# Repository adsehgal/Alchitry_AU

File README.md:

# Alchitry AU Shields
### Aditya Sehgal

</p>This repo is a compilation of custom shields I have designed for the Alchitry AU FPGA.</br>
The following is a list of shields I have designed:</p>
  <il>
   
 - [Alchitry PCB Template : ](https://github.com/adsehgal/Alchitry_AU/tree/master/KiCad_Template_Alchitry_Base_Top_Bot) KiCad template for the FPGA board, provided by Alchitry

 - [I/O Shield with HDMI : ](https://github.com/adsehgal/Alchitry_AU/tree/master/IO_Shield_W_HDMI) I/O shield with a variety of peripherals including an LED matrix and HDMI. Uses original Alchitry connectors
 - [Play Shield : ](https://github.com/adsehgal/Alchitry_AU/tree/master/Alchitry_Play_Shield) Shield designed to work like a controller with two sets of directional arrow keys, 7-segment displays, LED array and HDMI.

 The following is a list of boards I designed with a 1mm pitch connector instead of the original connectors that Alchitry uses:
  - [Connector Adaptor :](https://github.com/adsehgal/Alchitry_AU/tree/master/Alchitry_AU_Connector_Adaptor) Adaptor board to convert the 0.5mm standard mezzanine connectors to 1mm pitch connectors
 - [I/O Shield with 1mm connectors :](https://github.com/adsehgal/Alchitry_AU/tree/master/Alchitry_AU_NonStandard_IO) I/O shield with a variety of peripherals, used in conjunction with ["Connector Adaptor PCB"](https://github.com/adsehgal/Alchitry_AU/tree/master/Alchitry_AU_Connector_Adaptor)

 <il>
<br>

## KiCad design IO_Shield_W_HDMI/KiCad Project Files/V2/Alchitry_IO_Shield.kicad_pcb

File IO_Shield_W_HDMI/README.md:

# Alchitry AU Shields
### Aditya Sehgal

</p>This is a shiled I designed for the Alchitry AU development board with an LED matrix, dip switches, 7 segment displays and HDMI output</p>

## Updates 
- [x] Fix transistors for 7 segments
- [x] Potentially add a 4th 7 segment
- [x] Add pull downs to switches
- [x] Remove board connectors from top
- [x] Make LED matrix a square - 6x6?
- [ ] Potentially make 7 segments out of discrete LEDs
- [ ] Breakout headers for UART, I2C and SPI?
- [ ] Potentially add push buttons
- [ ] Increase series resistance for LED matrix
- [ ] Use diffused LEDs

<br>

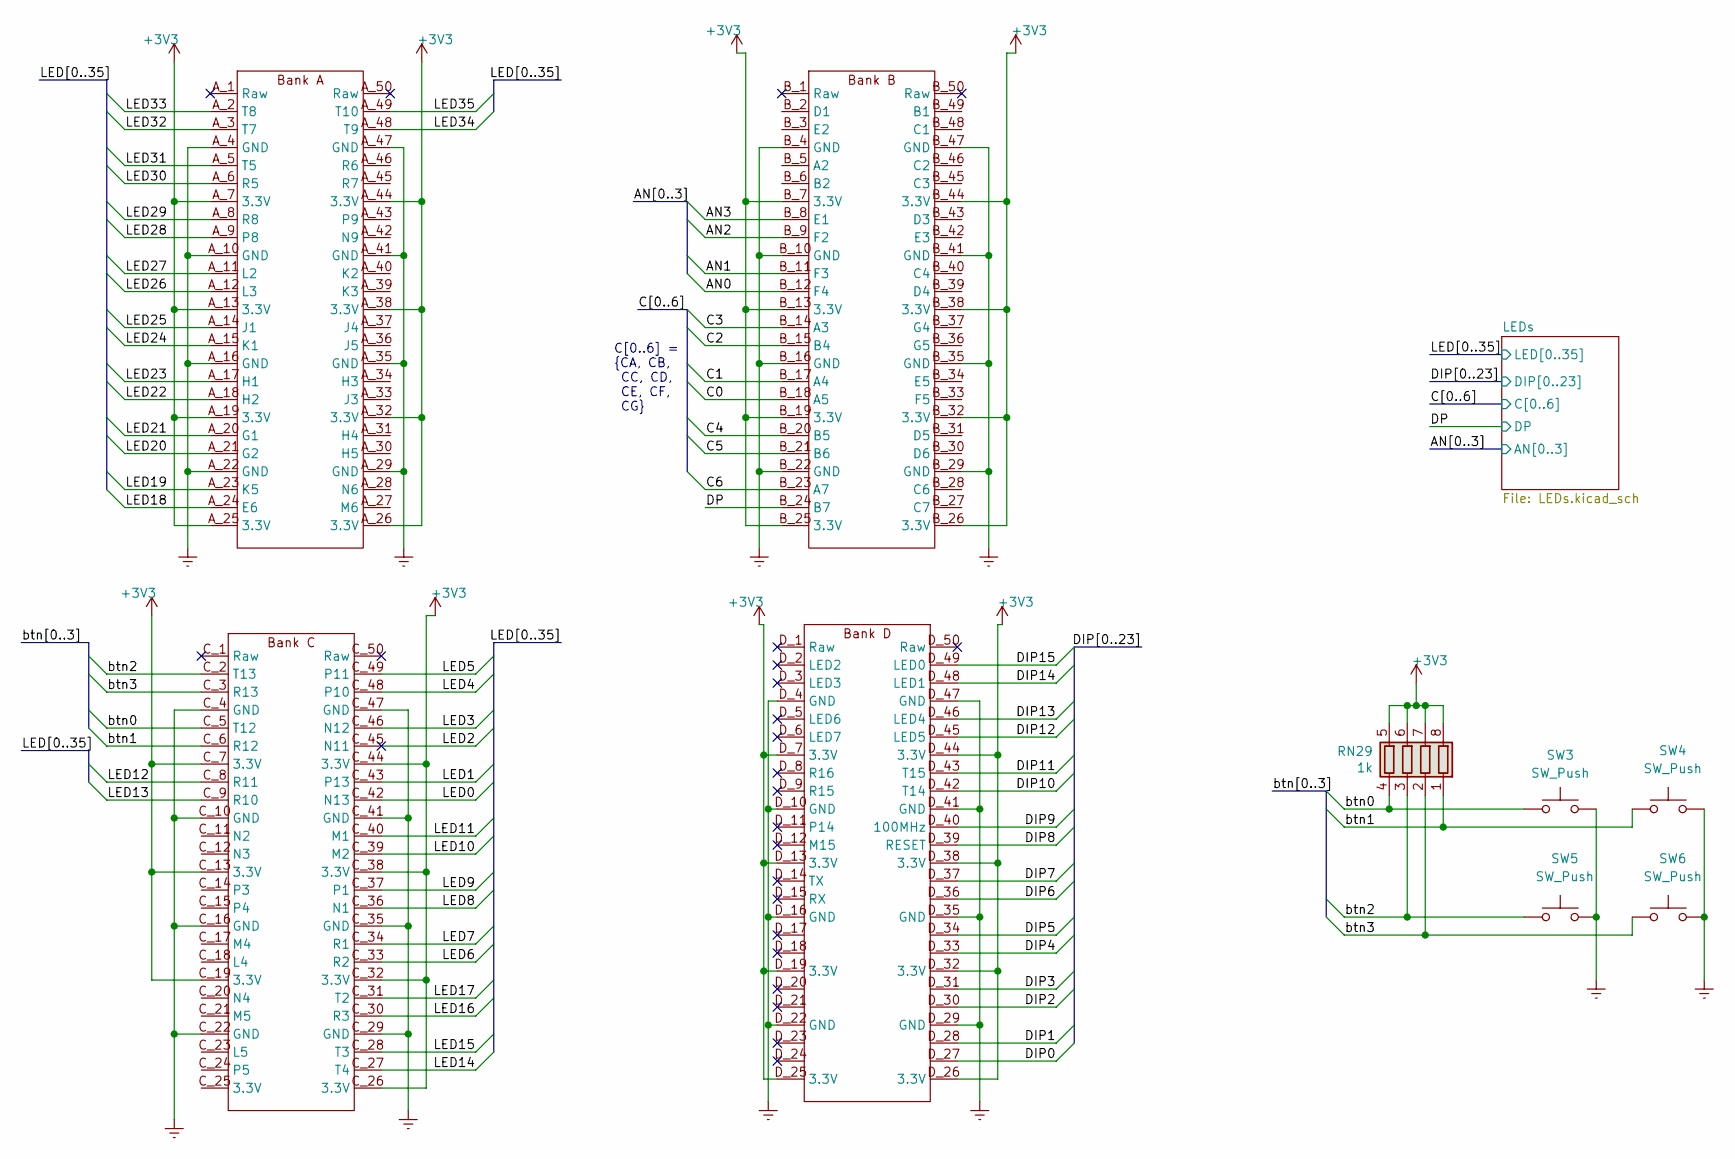
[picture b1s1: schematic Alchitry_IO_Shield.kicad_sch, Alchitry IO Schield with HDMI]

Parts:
RN29: 1k; R_Array_Convex_4x0603
SW3, SW4, SW5, SW6: SW_Push; SW_SPST_TL3342
U1: Alchitry_Single; Alchitry_Bottom

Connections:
+3V3: RN29.5 (R4.2), RN29.6 (R3.2), RN29.7 (R2.2), RN29.8 (R1.2), U1.A_7 (3.3V), U1.A_13 (3.3V), U1.A_19 (3.3V), U1.A_25 (3.3V), U1.A_26 (3.3V), U1.A_32 (3.3V), U1.A_38 (3.3V), U1.A_44 (3.3V), U1.B_7 (3.3V), U1.B_13 (3.3V), U1.B_19 (3.3V), U1.B_25 (3.3V), U1.B_26 (3.3V), U1.B_32 (3.3V), U1.B_38 (3.3V), U1.B_44 (3.3V), U1.C_7 (3.3V), U1.C_13 (3.3V), U1.C_19 (3.3V), U1.C_26 (3.3V), U1.C_32 (3.3V), U1.C_38 (3.3V), U1.C_44 (3.3V), U1.D_7 (3.3V), U1.D_13 (3.3V), U1.D_19 (3.3V), U1.D_25 (3.3V), U1.D_26 (3.3V), U1.D_32 (3.3V), U1.D_38 (3.3V), U1.D_44 (3.3V); also elsewhere on the board
/AN0: U1.B_12 (F4); also elsewhere on the board
/AN1: U1.B_11 (F3); also elsewhere on the board
/AN2: U1.B_9 (F2); also elsewhere on the board
/AN3: U1.B_8 (E1); also elsewhere on the board
/C0: U1.B_18 (A5); also elsewhere on the board
/C1: U1.B_17 (A4); also elsewhere on the board
/C2: U1.B_15 (B4); also elsewhere on the board
/C3: U1.B_14 (A3); also elsewhere on the board
/C4: U1.B_20 (B5); also elsewhere on the board
/C5: U1.B_21 (B6); also elsewhere on the board
/C6: U1.B_23 (A7); also elsewhere on the board
/DIP0: U1.D_27; also elsewhere on the board
/DIP1: U1.D_28; also elsewhere on the board
/DIP2: U1.D_30; also elsewhere on the board
/DIP3: U1.D_31; also elsewhere on the board
/DIP4: U1.D_33; also elsewhere on the board
/DIP5: U1.D_34; also elsewhere on the board
/DIP6: U1.D_36; also elsewhere on the board
/DIP7: U1.D_37; also elsewhere on the board
/DIP8: U1.D_39 (RESET); also elsewhere on the board
/DIP9: U1.D_40 (100MHz); also elsewhere on the board
/DIP10: U1.D_42 (T14); also elsewhere on the board
/DIP11: U1.D_43 (T15); also elsewhere on the board
/DIP12: U1.D_45 (LED5); also elsewhere on the board
/DIP13: U1.D_46 (LED4); also elsewhere on the board
/DIP14: U1.D_48 (LED1); also elsewhere on the board
/DIP15: U1.D_49 (LED0); also elsewhere on the board
/DP: U1.B_24 (B7); also elsewhere on the board
/LED0: U1.C_42 (N13); also elsewhere on the board
/LED1: U1.C_43 (P13); also elsewhere on the board
/LED2: U1.C_45 (N11); also elsewhere on the board
/LED3: U1.C_46 (N12); also elsewhere on the board
/LED4: U1.C_48 (P10); also elsewhere on the board
/LED5: U1.C_49 (P11); also elsewhere on the board
/LED6: U1.C_33 (R2); also elsewhere on the board
/LED7: U1.C_34 (R1); also elsewhere on the board
/LED8: U1.C_36 (N1); also elsewhere on the board
/LED9: U1.C_37 (P1); also elsewhere on the board
/LED10: U1.C_39 (M2); also elsewhere on the board
/LED11: U1.C_40 (M1); also elsewhere on the board
/LED12: U1.C_8 (R11); also elsewhere on the board
/LED13: U1.C_9 (R10); also elsewhere on the board
/LED14: U1.C_27 (T4); also elsewhere on the board
/LED15: U1.C_28 (T3); also elsewhere on the board
/LED16: U1.C_30 (R3); also elsewhere on the board
/LED17: U1.C_31 (T2); also elsewhere on the board
/LED18: U1.A_24 (E6); also elsewhere on the board
/LED19: U1.A_23 (K5); also elsewhere on the board
/LED20: U1.A_21 (G2); also elsewhere on the board
/LED21: U1.A_20 (G1); also elsewhere on the board
/LED22: U1.A_18 (H2); also elsewhere on the board
/LED23: U1.A_17 (H1); also elsewhere on the board
/LED24: U1.A_15 (K1); also elsewhere on the board
/LED25: U1.A_14 (J1); also elsewhere on the board
/LED26: U1.A_12 (L3); also elsewhere on the board
/LED27: U1.A_11 (L2); also elsewhere on the board
/LED28: U1.A_9 (P8); also elsewhere on the board
/LED29: U1.A_8 (R8); also elsewhere on the board
/LED30: U1.A_6 (R5); also elsewhere on the board
/LED31: U1.A_5 (T5); also elsewhere on the board
/LED32: U1.A_3 (T7); also elsewhere on the board
/LED33: U1.A_2 (T8); also elsewhere on the board
/LED34: U1.A_48 (T9); also elsewhere on the board
/LED35: U1.A_49 (T10); also elsewhere on the board
/btn0: RN29.4 (R4.1), SW3.1, U1.C_5 (T12)
/btn1: RN29.1 (R1.1), SW4.1, U1.C_6 (R12)
/btn2: RN29.3 (R3.1), SW5.1, U1.C_2 (T13)
/btn3: RN29.2 (R2.1), SW6.1, U1.C_3 (R13)
GNDREF: SW3.2, SW4.2, SW5.2, SW6.2, U1.A_4 (GND), U1.A_10 (GND), U1.A_16 (GND), U1.A_22 (GND), U1.A_29 (GND), U1.A_35 (GND), U1.A_41 (GND), U1.A_47 (GND), U1.B_4 (GND), U1.B_10 (GND), U1.B_16 (GND), U1.B_22 (GND), U1.B_29 (GND), U1.B_35 (GND), U1.B_41 (GND), U1.B_47 (GND), U1.C_4 (GND), U1.C_10 (GND), U1.C_16 (GND), U1.C_22 (GND), U1.C_29 (GND), U1.C_35 (GND), U1.C_41 (GND), U1.C_47 (GND), U1.D_4 (GND), U1.D_10 (GND), U1.D_16 (GND), U1.D_22 (GND), U1.D_29 (GND), U1.D_35 (GND), U1.D_41 (GND), U1.D_47 (GND); also elsewhere on the board

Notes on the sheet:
C[0..6] = {CA, CB, CC, CD, CE, CF, CG}

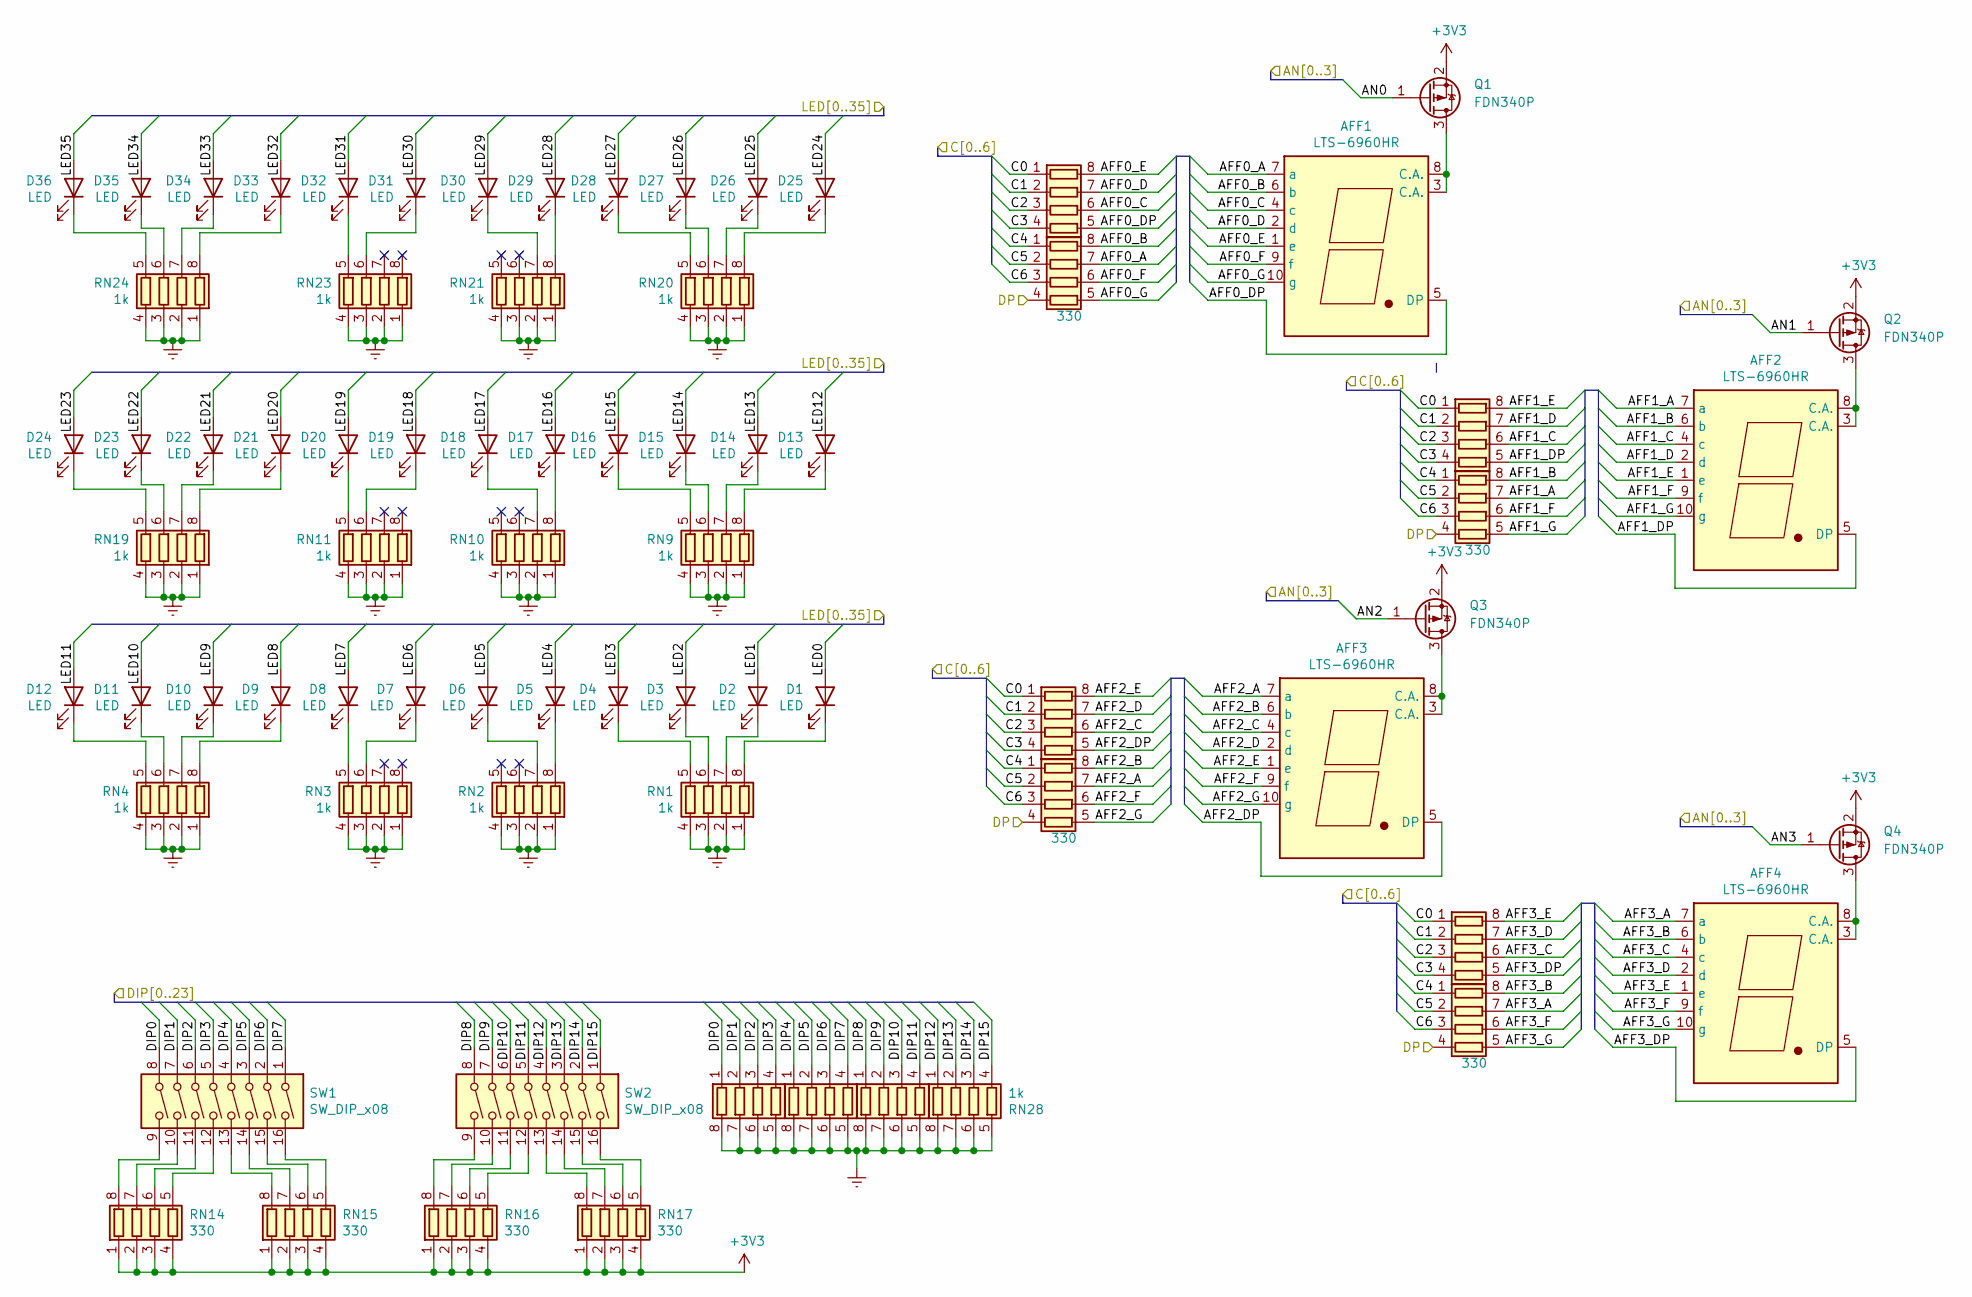
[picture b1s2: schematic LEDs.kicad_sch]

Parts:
AFF1, AFF2, AFF3, AFF4: LTS-6960HR; KCSC02-136
D1, D2, D3, D4, D5, D6, D7, D8, D9, D10, D11, D12, D13, D14, D15, D16, D17, D18, D19, D20, D21, D22, D23, D24, D25, D26, D27, D28, D29, D30, D31, D32, D33, D34, D35, D36: LED; LED_0603_1608Metric
Q1, Q2, Q3, Q4: FDN340P; SOT-23
RN1, RN2, RN3, RN4, RN9, RN10, RN11, RN19, RN20, RN21, RN23, RN24, RN28: 1k; R_Array_Convex_4x0603
RN5, RN6, RN12, RN18: R_Pack04; R_Array_Convex_4x0603
RN7, RN8, RN13, RN14, RN15, RN16, RN17, RN22, RN25, RN26, RN27: 330; R_Array_Convex_4x0603
SW1, SW2: SW_DIP_x08; SW_DIP_SPSTx08_Slide_Copal_CHS-08B_W7.62mm_P1.27mm

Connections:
+3V3: Q1.2 (S), Q2.2 (S), Q3.2 (S), Q4.2 (S), RN14.1 (R1.1), RN14.2 (R2.1), RN14.3 (R3.1), RN14.4 (R4.1), RN15.1 (R1.1), RN15.2 (R2.1), RN15.3 (R3.1), RN15.4 (R4.1), RN16.1 (R1.1), RN16.2 (R2.1), RN16.3 (R3.1), RN16.4 (R4.1), RN17.1 (R1.1), RN17.2 (R2.1), RN17.3 (R3.1), RN17.4 (R4.1); also elsewhere on the board
/AN0: Q1.1 (G); also elsewhere on the board
/AN1: Q2.1 (G); also elsewhere on the board
/AN2: Q3.1 (G); also elsewhere on the board
/AN3: Q4.1 (G); also elsewhere on the board
/C0: RN5.1 (R1.1), RN6.1 (R1.1), RN12.1 (R1.1), RN18.1 (R1.1); also elsewhere on the board
/C1: RN5.2 (R2.1), RN6.2 (R2.1), RN12.2 (R2.1), RN18.2 (R2.1); also elsewhere on the board
/C2: RN5.3 (R3.1), RN6.3 (R3.1), RN12.3 (R3.1), RN18.3 (R3.1); also elsewhere on the board
/C3: RN5.4 (R4.1), RN6.4 (R4.1), RN12.4 (R4.1), RN18.4 (R4.1); also elsewhere on the board
/C4: RN7.1 (R1.1), RN8.1 (R1.1), RN13.1 (R1.1), RN22.1 (R1.1); also elsewhere on the board
/C5: RN7.2 (R2.1), RN8.2 (R2.1), RN13.2 (R2.1), RN22.2 (R2.1); also elsewhere on the board
/C6: RN7.3 (R3.1), RN8.3 (R3.1), RN13.3 (R3.1), RN22.3 (R3.1); also elsewhere on the board
/DIP0: RN25.1 (R1.1), SW1.8; also elsewhere on the board
/DIP1: RN25.2 (R2.1), SW1.7; also elsewhere on the board
/DIP2: RN25.3 (R3.1), SW1.6; also elsewhere on the board
/DIP3: RN25.4 (R4.1), SW1.5; also elsewhere on the board
/DIP4: RN26.1 (R1.1), SW1.4; also elsewhere on the board
/DIP5: RN26.2 (R2.1), SW1.3; also elsewhere on the board
/DIP6: RN26.3 (R3.1), SW1.2; also elsewhere on the board
/DIP7: RN26.4 (R4.1), SW1.1; also elsewhere on the board
/DIP8: RN27.1 (R1.1), SW2.8; also elsewhere on the board
/DIP9: RN27.2 (R2.1), SW2.7; also elsewhere on the board
/DIP10: RN27.3 (R3.1), SW2.6; also elsewhere on the board
/DIP11: RN27.4 (R4.1), SW2.5; also elsewhere on the board
/DIP12: RN28.1 (R1.1), SW2.4; also elsewhere on the board
/DIP13: RN28.2 (R2.1), SW2.3; also elsewhere on the board
/DIP14: RN28.3 (R3.1), SW2.2; also elsewhere on the board
/DIP15: RN28.4 (R4.1), SW2.1; also elsewhere on the board
/DP: RN7.4 (R4.1), RN8.4 (R4.1), RN13.4 (R4.1), RN22.4 (R4.1); also elsewhere on the board
/LED0: D1.2 (A); also elsewhere on the board
/LED1: D2.2 (A); also elsewhere on the board
/LED2: D3.2 (A); also elsewhere on the board
/LED3: D4.2 (A); also elsewhere on the board
/LED4: D5.2 (A); also elsewhere on the board
/LED5: D6.2 (A); also elsewhere on the board
/LED6: D7.2 (A); also elsewhere on the board
/LED7: D8.2 (A); also elsewhere on the board
/LED8: D9.2 (A); also elsewhere on the board
/LED9: D10.2 (A); also elsewhere on the board
/LED10: D11.2 (A); also elsewhere on the board
/LED11: D12.2 (A); also elsewhere on the board
/LED12: D13.2 (A); also elsewhere on the board
/LED13: D14.2 (A); also elsewhere on the board
/LED14: D15.2 (A); also elsewhere on the board
/LED15: D16.2 (A); also elsewhere on the board
/LED16: D17.2 (A); also elsewhere on the board
/LED17: D18.2 (A); also elsewhere on the board
/LED18: D19.2 (A); also elsewhere on the board
/LED19: D20.2 (A); also elsewhere on the board
/LED20: D21.2 (A); also elsewhere on the board
/LED21: D22.2 (A); also elsewhere on the board
/LED22: D23.2 (A); also elsewhere on the board
/LED23: D24.2 (A); also elsewhere on the board
/LED24: D25.2 (A); also elsewhere on the board
/LED25: D26.2 (A); also elsewhere on the board
/LED26: D27.2 (A); also elsewhere on the board
/LED27: D28.2 (A); also elsewhere on the board
/LED28: D29.2 (A); also elsewhere on the board
/LED29: D30.2 (A); also elsewhere on the board
/LED30: D31.2 (A); also elsewhere on the board
/LED31: D32.2 (A); also elsewhere on the board
/LED32: D33.2 (A); also elsewhere on the board
/LED33: D34.2 (A); also elsewhere on the board
/LED34: D35.2 (A); also elsewhere on the board
/LED35: D36.2 (A); also elsewhere on the board
/LEDs/AFF0_A: AFF1.7 (a), RN7.7 (R2.2)
/LEDs/AFF0_B: AFF1.6 (b), RN7.8 (R1.2)
/LEDs/AFF0_C: AFF1.4 (c), RN5.6 (R3.2)
/LEDs/AFF0_D: AFF1.2 (d), RN5.7 (R2.2)
/LEDs/AFF0_DP: AFF1.5 (DP), RN5.5 (R4.2)
/LEDs/AFF0_E: AFF1.1 (e), RN5.8 (R1.2)
/LEDs/AFF0_F: AFF1.9 (f), RN7.6 (R3.2)
/LEDs/AFF0_G: AFF1.10 (g), RN7.5 (R4.2)
/LEDs/AFF1_A: AFF2.7 (a), RN8.7 (R2.2)
/LEDs/AFF1_B: AFF2.6 (b), RN8.8 (R1.2)
/LEDs/AFF1_C: AFF2.4 (c), RN6.6 (R3.2)
/LEDs/AFF1_D: AFF2.2 (d), RN6.7 (R2.2)
/LEDs/AFF1_DP: AFF2.5 (DP), RN6.5 (R4.2)
/LEDs/AFF1_E: AFF2.1 (e), RN6.8 (R1.2)
/LEDs/AFF1_F: AFF2.9 (f), RN8.6 (R3.2)
/LEDs/AFF1_G: AFF2.10 (g), RN8.5 (R4.2)
/LEDs/AFF2_A: AFF3.7 (a), RN13.7 (R2.2)
/LEDs/AFF2_B: AFF3.6 (b), RN13.8 (R1.2)
/LEDs/AFF2_C: AFF3.4 (c), RN12.6 (R3.2)
/LEDs/AFF2_D: AFF3.2 (d), RN12.7 (R2.2)
/LEDs/AFF2_DP: AFF3.5 (DP), RN12.5 (R4.2)
/LEDs/AFF2_E: AFF3.1 (e), RN12.8 (R1.2)
/LEDs/AFF2_F: AFF3.9 (f), RN13.6 (R3.2)
/LEDs/AFF2_G: AFF3.10 (g), RN13.5 (R4.2)
/LEDs/AFF3_A: AFF4.7 (a), RN22.7 (R2.2)
/LEDs/AFF3_B: AFF4.6 (b), RN22.8 (R1.2)
/LEDs/AFF3_C: AFF4.4 (c), RN18.6 (R3.2)
/LEDs/AFF3_D: AFF4.2 (d), RN18.7 (R2.2)
/LEDs/AFF3_DP: AFF4.5 (DP), RN18.5 (R4.2)
/LEDs/AFF3_E: AFF4.1 (e), RN18.8 (R1.2)
/LEDs/AFF3_F: AFF4.9 (f), RN22.6 (R3.2)
/LEDs/AFF3_G: AFF4.10 (g), RN22.5 (R4.2)
GNDREF: RN1.1 (R1.1), RN1.2 (R2.1), RN1.3 (R3.1), RN1.4 (R4.1), RN2.1 (R1.1), RN2.2 (R2.1), RN2.3 (R3.1), RN2.4 (R4.1), RN3.1 (R1.1), RN3.2 (R2.1), RN3.3 (R3.1), RN3.4 (R4.1), RN4.1 (R1.1), RN4.2 (R2.1), RN4.3 (R3.1), RN4.4 (R4.1), RN9.1 (R1.1), RN9.2 (R2.1), RN9.3 (R3.1), RN9.4 (R4.1), RN10.1 (R1.1), RN10.2 (R2.1), RN10.3 (R3.1), RN10.4 (R4.1), RN11.1 (R1.1), RN11.2 (R2.1), RN11.3 (R3.1), RN11.4 (R4.1), RN19.1 (R1.1), RN19.2 (R2.1), RN19.3 (R3.1), RN19.4 (R4.1), RN20.1 (R1.1), RN20.2 (R2.1), RN20.3 (R3.1), RN20.4 (R4.1), RN21.1 (R1.1), RN21.2 (R2.1), RN21.3 (R3.1), RN21.4 (R4.1), RN23.1 (R1.1), RN23.2 (R2.1), RN23.3 (R3.1), RN23.4 (R4.1), RN24.1 (R1.1), RN24.2 (R2.1), RN24.3 (R3.1), RN24.4 (R4.1), RN25.5 (R4.2), RN25.6 (R3.2), RN25.7 (R2.2), RN25.8 (R1.2), RN26.5 (R4.2), RN26.6 (R3.2), RN26.7 (R2.2), RN26.8 (R1.2), RN27.5 (R4.2), RN27.6 (R3.2), RN27.7 (R2.2), RN27.8 (R1.2), RN28.5 (R4.2), RN28.6 (R3.2), RN28.7 (R2.2), RN28.8 (R1.2); also elsewhere on the board
unnamed: AFF1.3 (C.A.), AFF1.8 (C.A.), Q1.3 (D)
unnamed: AFF2.3 (C.A.), AFF2.8 (C.A.), Q2.3 (D)
unnamed: AFF3.3 (C.A.), AFF3.8 (C.A.), Q3.3 (D)
unnamed: AFF4.3 (C.A.), AFF4.8 (C.A.), Q4.3 (D)
unnamed: D1.1 (K), RN1.8 (R1.2)
unnamed: D2.1 (K), RN1.7 (R2.2)
unnamed: D3.1 (K), RN1.6 (R3.2)
unnamed: D4.1 (K), RN1.5 (R4.2)
unnamed: D5.1 (K), RN2.8 (R1.2)
unnamed: D6.1 (K), RN2.7 (R2.2)
unnamed: D7.1 (K), RN3.6 (R3.2)
unnamed: D8.1 (K), RN3.5 (R4.2)
unnamed: D9.1 (K), RN4.8 (R1.2)
unnamed: D10.1 (K), RN4.7 (R2.2)
unnamed: D11.1 (K), RN4.6 (R3.2)
unnamed: D12.1 (K), RN4.5 (R4.2)
unnamed: D13.1 (K), RN9.8 (R1.2)
unnamed: D14.1 (K), RN9.7 (R2.2)
unnamed: D15.1 (K), RN9.6 (R3.2)
unnamed: D16.1 (K), RN9.5 (R4.2)
unnamed: D17.1 (K), RN10.8 (R1.2)
unnamed: D18.1 (K), RN10.7 (R2.2)
unnamed: D19.1 (K), RN11.6 (R3.2)
unnamed: D20.1 (K), RN11.5 (R4.2)
unnamed: D21.1 (K), RN19.8 (R1.2)
unnamed: D22.1 (K), RN19.7 (R2.2)
unnamed: D23.1 (K), RN19.6 (R3.2)
unnamed: D24.1 (K), RN19.5 (R4.2)
unnamed: D25.1 (K), RN20.8 (R1.2)
unnamed: D26.1 (K), RN20.7 (R2.2)
unnamed: D27.1 (K), RN20.6 (R3.2)
unnamed: D28.1 (K), RN20.5 (R4.2)
unnamed: D29.1 (K), RN21.8 (R1.2)
unnamed: D30.1 (K), RN21.7 (R2.2)
unnamed: D31.1 (K), RN23.6 (R3.2)
unnamed: D32.1 (K), RN23.5 (R4.2)
unnamed: D33.1 (K), RN24.8 (R1.2)
unnamed: D34.1 (K), RN24.7 (R2.2)
unnamed: D35.1 (K), RN24.6 (R3.2)
unnamed: D36.1 (K), RN24.5 (R4.2)
unnamed: RN14.5 (R4.2), SW1.12
unnamed: RN14.6 (R3.2), SW1.11
unnamed: RN14.7 (R2.2), SW1.10
unnamed: RN14.8 (R1.2), SW1.9
unnamed: RN15.5 (R4.2), SW1.16
unnamed: RN15.6 (R3.2), SW1.15
unnamed: RN15.7 (R2.2), SW1.14
unnamed: RN15.8 (R1.2), SW1.13
unnamed: RN16.5 (R4.2), SW2.12
unnamed: RN16.6 (R3.2), SW2.11
unnamed: RN16.7 (R2.2), SW2.10
unnamed: RN16.8 (R1.2), SW2.9
unnamed: RN17.5 (R4.2), SW2.16
unnamed: RN17.6 (R3.2), SW2.15
unnamed: RN17.7 (R2.2), SW2.14
unnamed: RN17.8 (R1.2), SW2.13

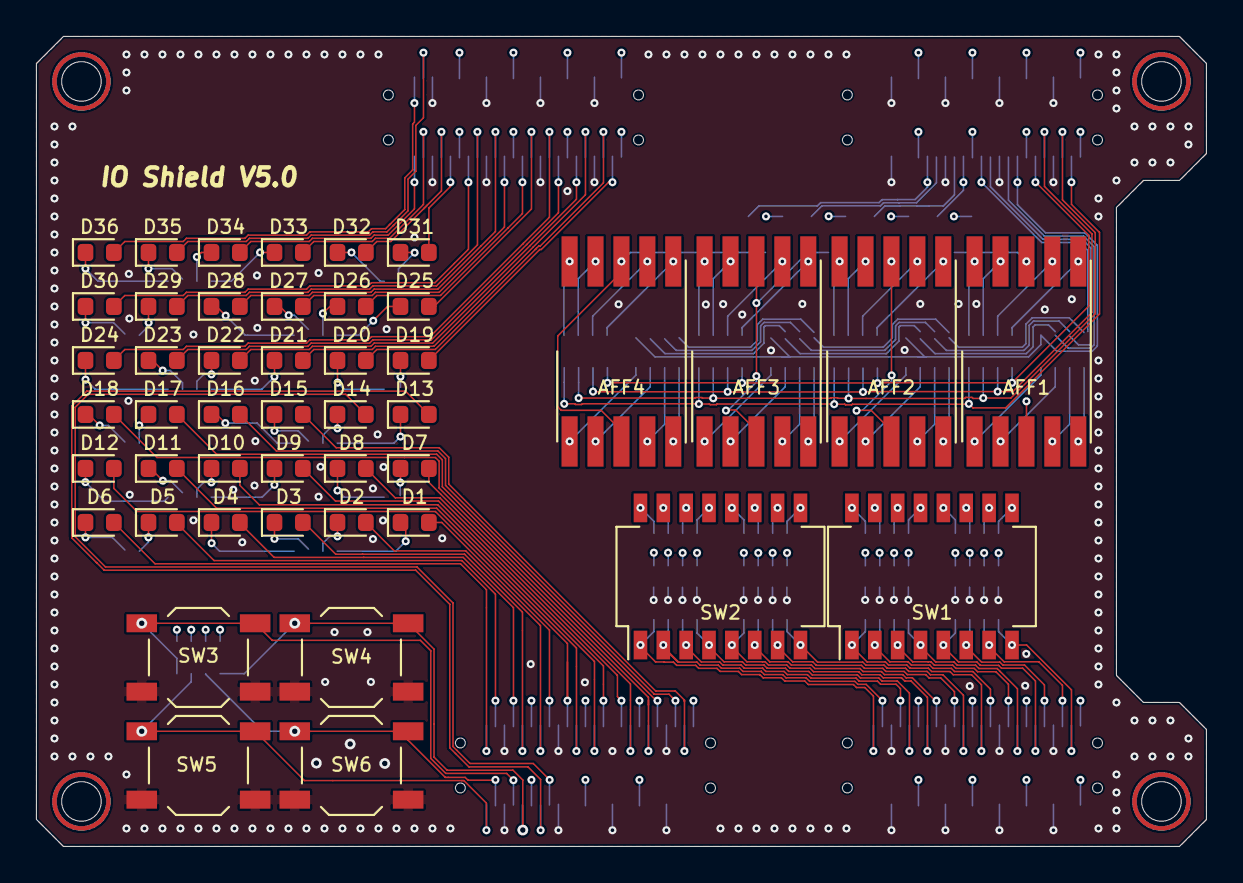
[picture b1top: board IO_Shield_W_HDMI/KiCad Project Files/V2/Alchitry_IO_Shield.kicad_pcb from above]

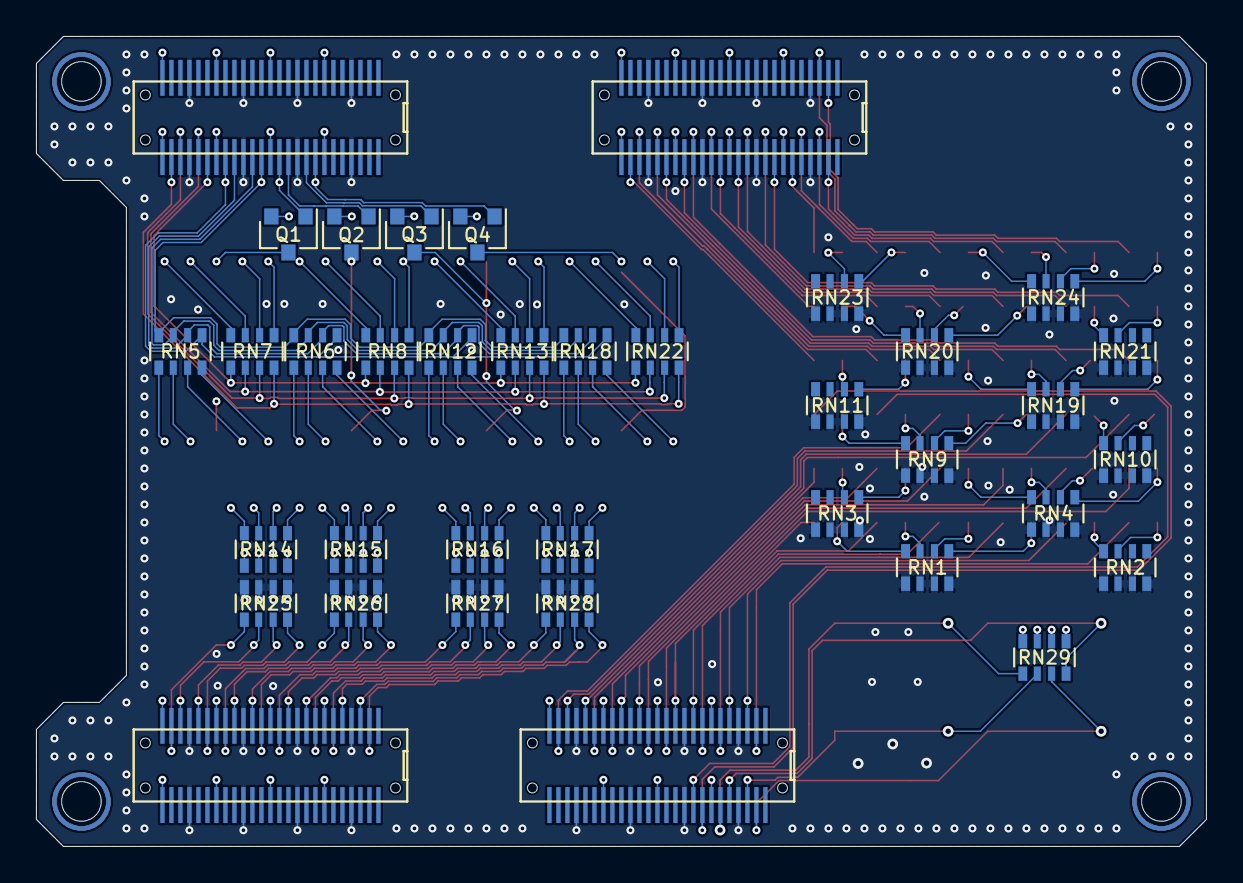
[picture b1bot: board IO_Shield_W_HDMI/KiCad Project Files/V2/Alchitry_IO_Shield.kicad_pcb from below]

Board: 4 copper layers, 65.0 x 45.0 mm, 80 parts (33 on the bottom side), 158 nets.
